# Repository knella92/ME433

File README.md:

# ME433
Advanced Mechatronics repo

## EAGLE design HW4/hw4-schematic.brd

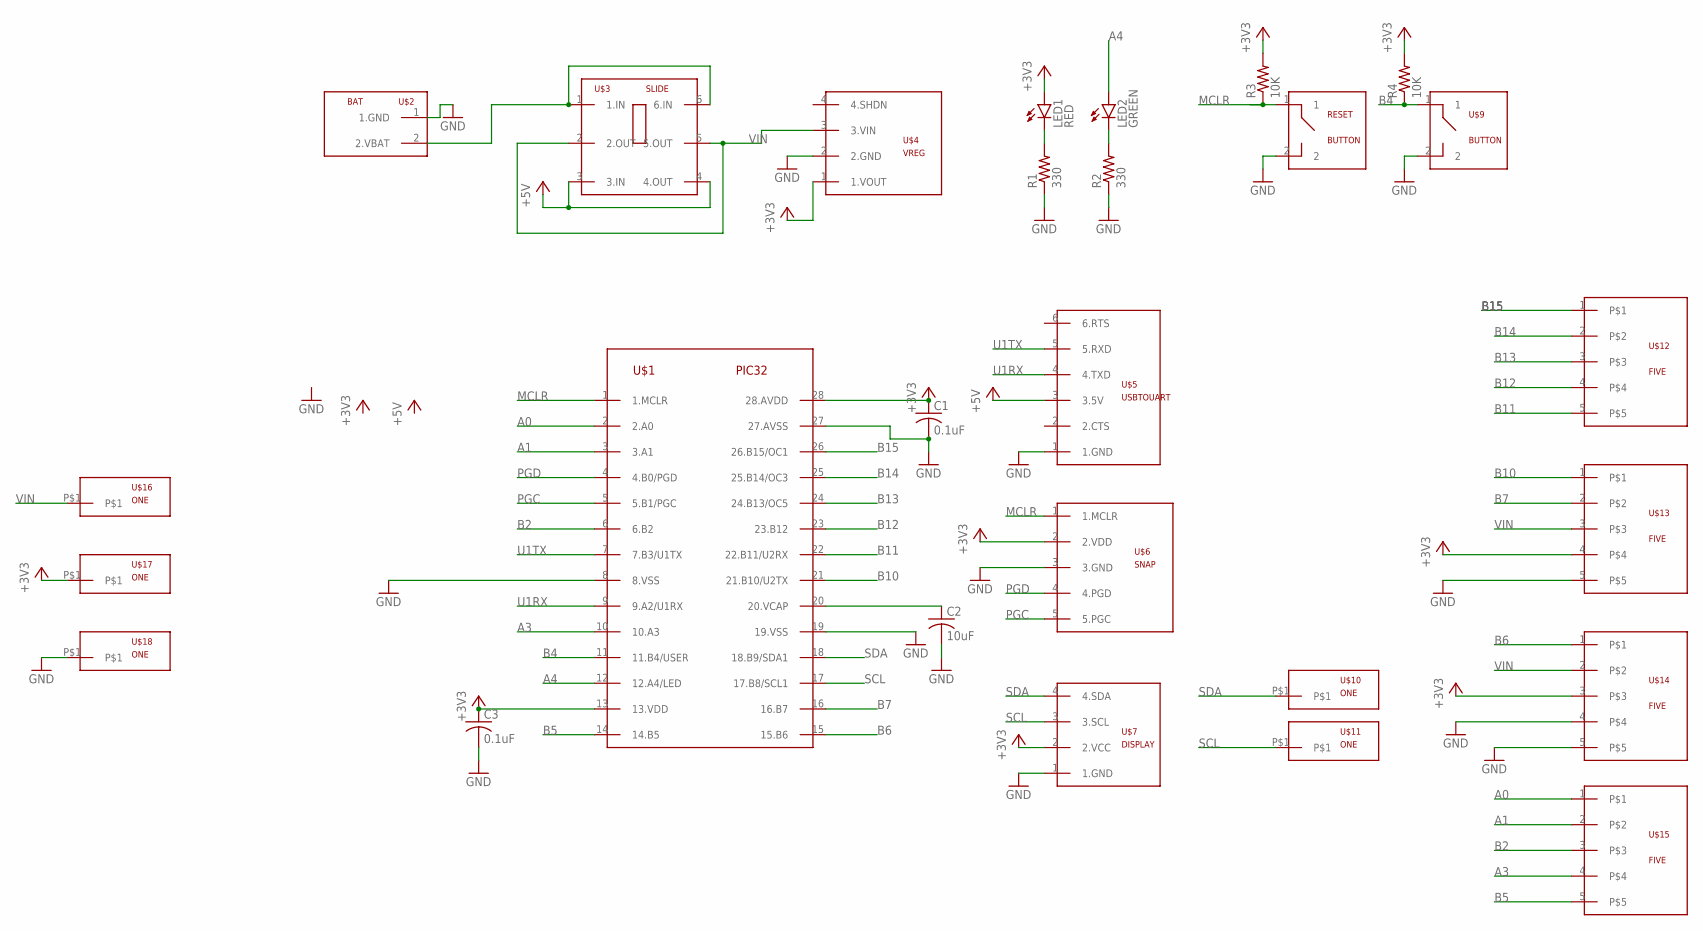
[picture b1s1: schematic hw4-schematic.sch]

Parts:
C1, C3: 0.1uF; C025-024X044
C2: 10uF; C025-024X044
LED1: RED; LED3MM
LED2: GREEN; LED3MM
R1, R2: 330; 0207/7
R3, R4: 10K; 0207/7
RESET: BUTTON
U$1: PIC32; DIL28-3
U$2: BAT
U$3: SLIDE
U$4: VREG
U$5: USBTOUART
U$6: SNAP
U$7: DISPLAY
U$9: BUTTON
U$10, U$11, U$16, U$17, U$18: ONE
U$12, U$13, U$14, U$15: FIVE

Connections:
+3V3: C1.1, C3.1, LED1.A, R3.2, R4.2, U$1.13 (13.VDD), U$1.28 (28.AVDD), U$4.1 (1.VOUT), U$6.2 (2.VDD), U$7.2 (2.VCC), U$13.4, U$14.3, U$17.P$1
+5V: U$3.3 (3.IN), U$3.4 (4.OUT), U$5.3 (3.5V)
A0: U$1.2 (2.A0), U$15.1
A1: U$1.3 (3.A1), U$15.2
A3: U$1.10 (10.A3), U$15.4
A4: LED2.A, U$1.12 (12.A4/LED)
B2: U$1.6 (6.B2), U$15.3
B4: R4.1, U$1.11 (11.B4/USER), U$9.1
B5: U$1.14 (14.B5), U$15.5
B6: U$1.15 (15.B6), U$14.1
B7: U$1.16 (16.B7), U$13.2
B10: U$1.21 (21.B10/U2TX), U$13.1
B11: U$1.22 (22.B11/U2RX), U$12.5
B12: U$1.23 (23.B12), U$12.4
B13: U$1.24 (24.B13/OC5), U$12.3
B14: U$1.25 (25.B14/OC3), U$12.2
B15: U$1.26 (26.B15/OC1), U$12.1
GND: C1.2, C2.2, C3.2, R1.1, R2.1, RESET.2, U$1.8 (8.VSS), U$1.19 (19.VSS), U$1.27 (27.AVSS), U$2.1 (1.GND), U$4.2 (2.GND), U$5.1 (1.GND), U$6.3 (3.GND), U$7.1 (1.GND), U$9.2, U$13.5, U$14.4, U$14.5, U$18.P$1
MCLR: R3.1, RESET.1, U$1.1 (1.MCLR), U$6.1 (1.MCLR)
unnamed: LED1.K (C), R1.2
unnamed: U$2.2 (2.VBAT), U$3.1 (1.IN), U$3.6 (6.IN)
unnamed: C2.1, U$1.20 (20.VCAP)
unnamed: LED2.K (C), R2.2
PGC: U$1.5 (5.B1/PGC), U$6.5 (5.PGC)
PGD: U$1.4 (4.B0/PGD), U$6.4 (4.PGD)
SCL: U$1.17 (17.B8/SCL1), U$7.3 (3.SCL), U$11.P$1
SDA: U$1.18 (18.B9/SDA1), U$7.4 (4.SDA), U$10.P$1
U1RX: U$1.9 (9.A2/U1RX), U$5.4 (4.TXD)
U1TX: U$1.7 (7.B3/U1TX), U$5.5 (5.RXD)
VIN: U$3.2 (2.OUT), U$3.5 (5.OUT), U$4.3 (3.VIN), U$13.3, U$14.2, U$16.P$1

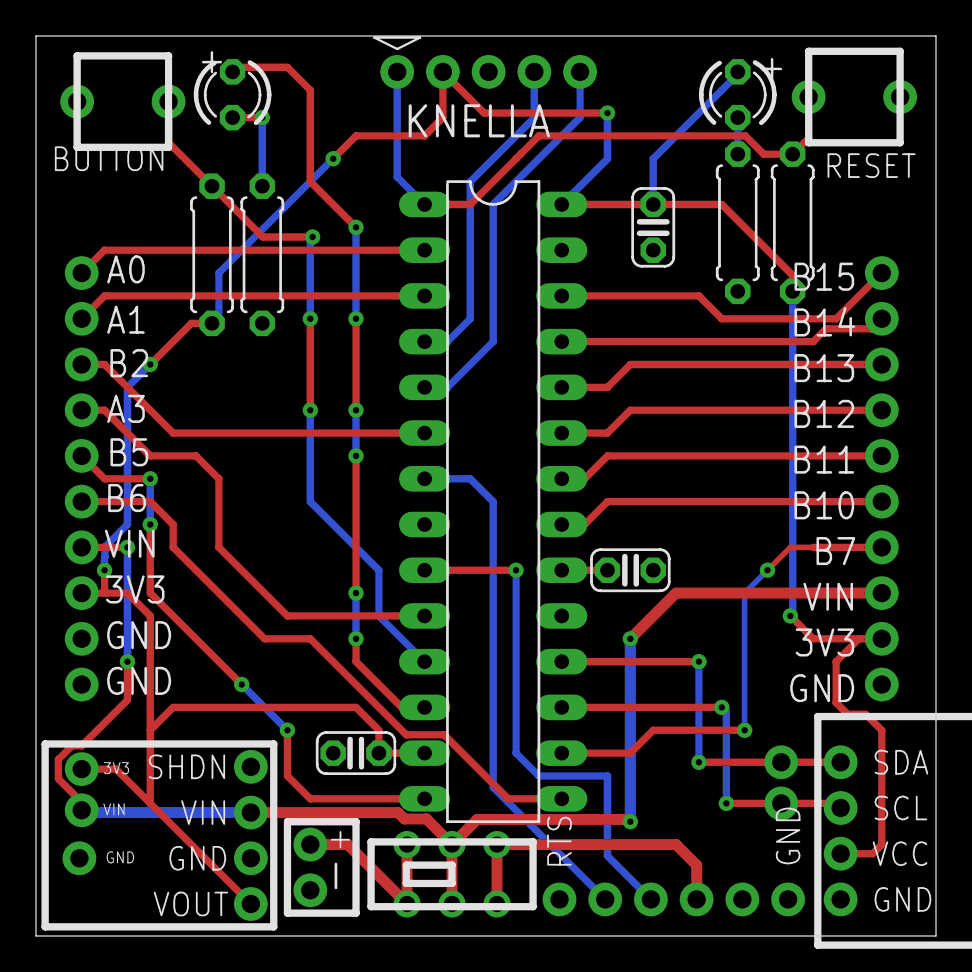
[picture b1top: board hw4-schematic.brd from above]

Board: 2 copper layers, 50.0 x 50.0 mm, 27 parts (0 on the bottom side), 30 nets.

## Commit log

2022-04-11 finalized
2022-04-11 added picture
2022-04-11 finalized hw3 code
2022-04-30 finished
2022-05-05 finished hw5
2022-05-14 finished hw6
2022-05-24 uart header file not working
2022-05-24 got provided code working
2022-06-07 finished hw8
2022-06-08 finished hw9
2022-06-09 dont know how to plot
2022-06-09 finished hw11
2022-06-09 added screenshots of hw11
2022-06-09 added screenshots for hw 11
2022-06-09 squaring things away
2022-06-09 hw10 done
2022-06-09 uploaded screen recording hw 10
2022-06-10 finished hw 7
